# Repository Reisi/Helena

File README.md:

# Helena

Helena is an alternative driver for the Yinding or KD2 Headlight Cycling Lamp.

## Main Features

- Two independant 3A Step-Down current converters.
- Bluetooth connectivity for remote control, configuration and lamp-to-lamp connection.
- Linear power reduction at low battery and high temperature.
- Standby current less than 150µA.
- Supports 1 (one LED), 2 (one or two LEDs) or 3 (up to three LEDs in series) cell Li-Ion battery.
- An integrated motion sensor to control the output current to reduce glare when looking down.
- A multi-functional com pin, can be used for wired communication or an external button.

## License

This project is licensed under the BSD-2-clause License - see the [license.txt](license.txt) file for details

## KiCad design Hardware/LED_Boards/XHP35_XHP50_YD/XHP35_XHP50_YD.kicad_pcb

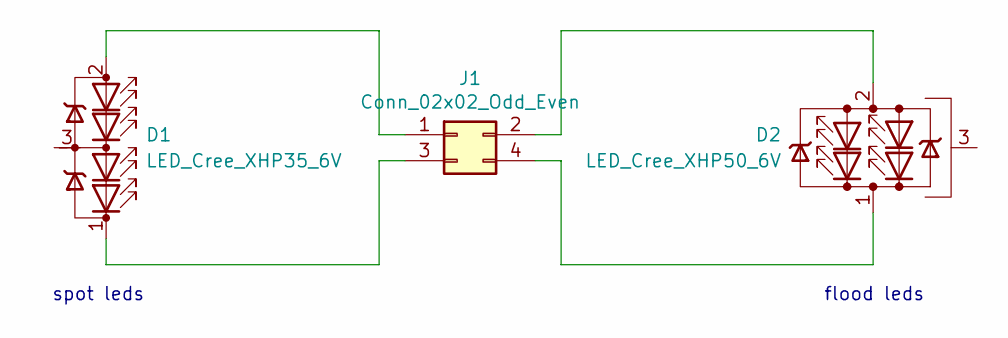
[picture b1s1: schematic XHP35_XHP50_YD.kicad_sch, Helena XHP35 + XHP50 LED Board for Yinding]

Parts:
D1: LED_Cree_XHP35_6V; LED_Cree-XHP50_12V
D2: LED_Cree_XHP50_6V; LED_Cree-XHP50_6V
J1: Conn_02x02_Odd_Even; PinHeader_2x02_P2.00mm_Vertical_SMD

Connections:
unnamed: D1.2 (A), J1.1
unnamed: D1.1 (K), J1.3
unnamed: D2.2 (A), J1.2
unnamed: D2.1 (K), J1.4

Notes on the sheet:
flood leds
spot leds

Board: 2 copper layers, 3 parts (0 on the bottom side), 4 nets, no tracks yet.

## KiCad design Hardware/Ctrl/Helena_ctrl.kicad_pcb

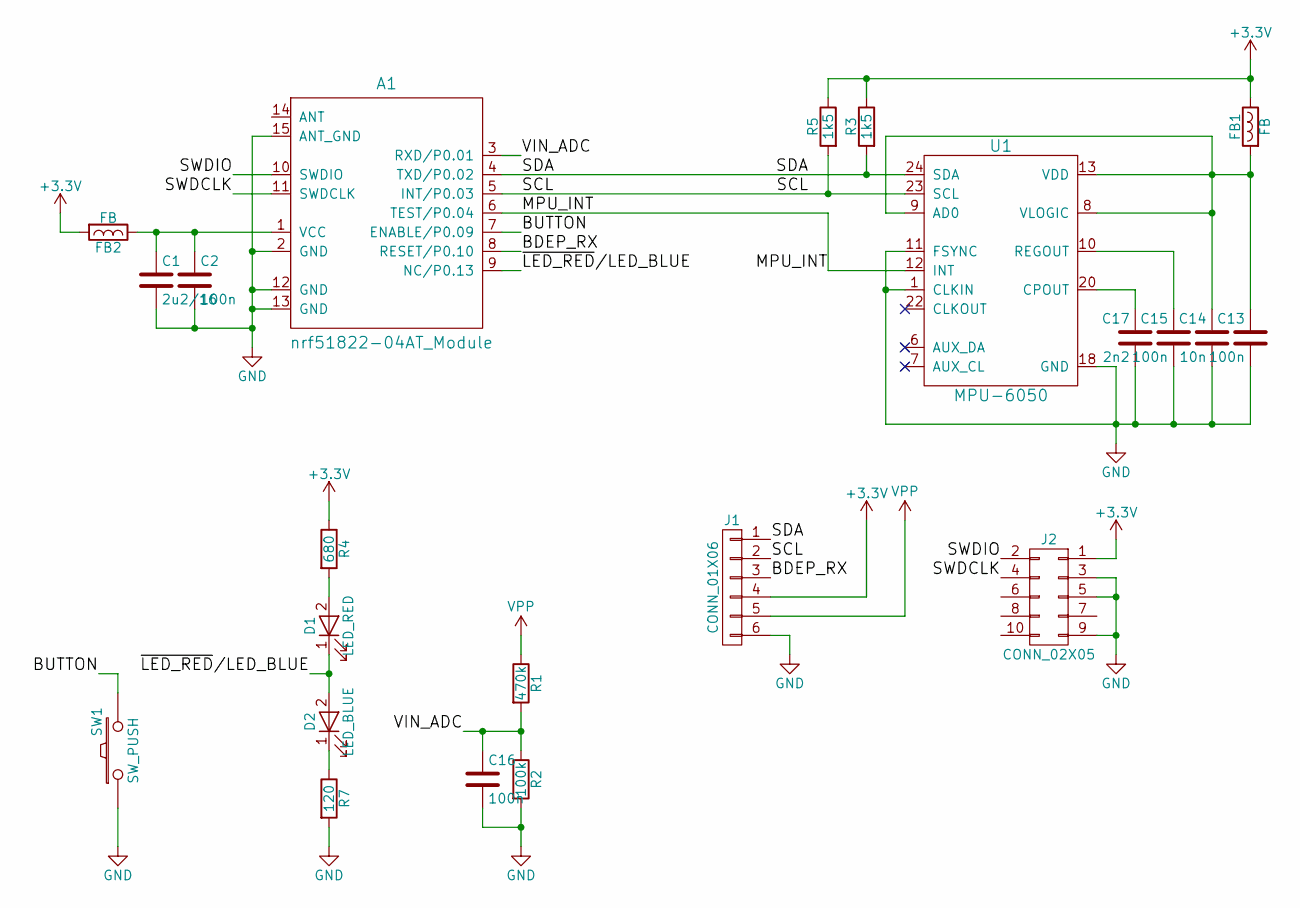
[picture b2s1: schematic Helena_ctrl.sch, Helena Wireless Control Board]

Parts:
A1: nrf51822-04AT_Module; WT51822-S4AT
C1: 2u2/16; C_0603_1608Metric
C2, C13, C15, C16: 100n; C_0603_1608Metric
C14: 10n; C_0603_1608Metric
C17: 2n2; C_0603_1608Metric
D1: LED_RED; D_0603_1608Metric
D2: LED_BLUE; D_0603_1608Metric
FB1, FB2: FB; L_0603_1608Metric
J1: CONN_01X06; PinHeader_1x06_P2.00mm_Vertical
J2: CONN_02X05; PinHeader_2x05_P1.27mm_Vertical
R1: 470k; R_0603_1608Metric
R2: 100k; R_0603_1608Metric
R3, R5: 1k5; R_0603_1608Metric
R4: 680; R_0603_1608Metric
R7: 120; R_0603_1608Metric
SW1: SW_PUSH; JTP-1138EM
U1: MPU-6050; QFN-24_4x4mm_Pitch0.5mm

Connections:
+3V3: FB1.1, FB2.2, J1.4, J2.1, R3.1, R4.1, R5.1
/BDEP_RX: A1.8 (RESET/P0.10), J1.3
/BUTTON: A1.7 (ENABLE/P0.09), SW1.2
/MPU_INT: A1.6 (TEST/P0.04), U1.12 (INT)
/SCL: A1.5 (INT/P0.03), J1.2, R5.2, U1.23 (SCL)
/SDA: A1.4 (TXD/P0.02), J1.1, R3.2, U1.24 (SDA)
/SWDCLK: A1.11 (SWDCLK), J2.4
/SWDIO: A1.10 (SWDIO), J2.2
/VIN_ADC: A1.3 (RXD/P0.01), C16.1, R1.2, R2.1
/~LED_RED~/LED_BLUE: A1.9 (NC/P0.13), D1.1 (K), D2.2 (A)
GND: A1.2 (GND), A1.12 (GND), A1.13 (GND), A1.15 (ANT_GND), C1.2, C2.2, C13.2, C14.2, C15.2, C16.2, C17.2, J1.6, J2.3, J2.5, J2.9, R2.2, R7.2, SW1.1, U1.1 (CLKIN), U1.11 (FSYNC), U1.18 (GND)
unnamed: A1.1 (VCC), C1.1, C2.1, FB2.1
unnamed: C13.1, C14.1, FB1.2, U1.8 (VLOGIC), U1.9 (AD0), U1.13 (VDD)
unnamed: C15.1, U1.10 (REGOUT)
unnamed: C17.1, U1.20 (CPOUT)
unnamed: D1.2 (A), R4.2
unnamed: D2.1 (K), R7.1
VPP: J1.5, R1.1

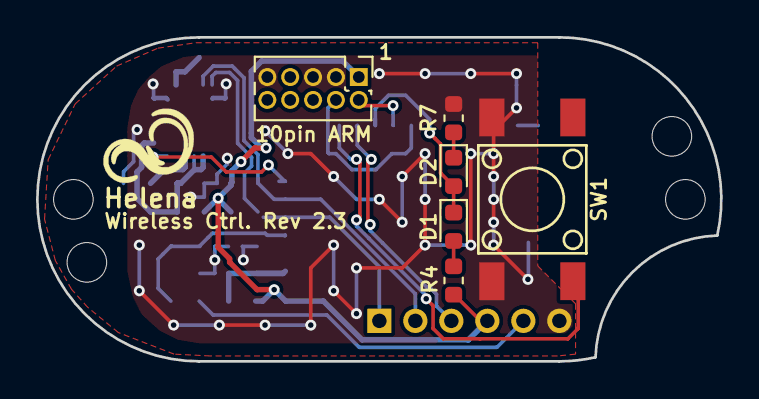
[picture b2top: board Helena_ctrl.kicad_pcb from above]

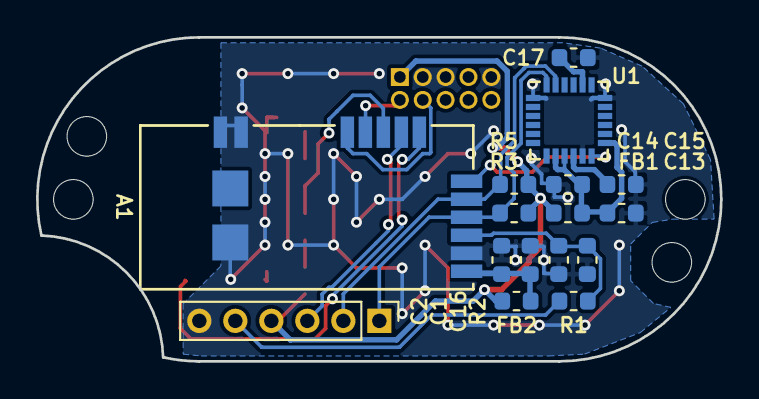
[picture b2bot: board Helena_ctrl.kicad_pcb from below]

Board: 2 copper layers, 38.0 x 18.0 mm, 22 parts (16 on the bottom side), 18 nets.

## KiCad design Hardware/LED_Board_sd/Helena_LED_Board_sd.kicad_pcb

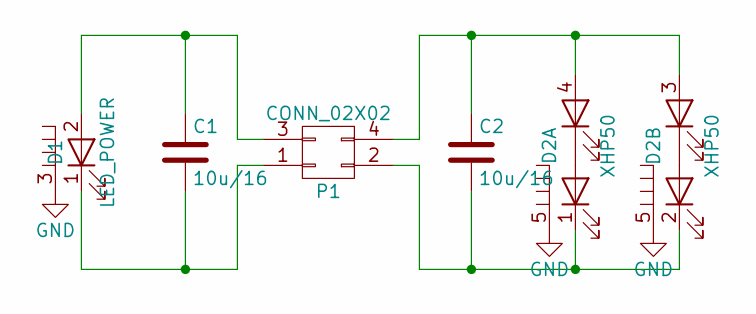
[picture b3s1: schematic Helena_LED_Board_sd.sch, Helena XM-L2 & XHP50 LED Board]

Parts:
C1, C2: 10u/16; C_0805
D1: LED_POWER; LED_CREE-XML
D2: XHP50; LED_CREE-XHP50
P1: CONN_02X02; Pin_Header_Straight_2x02_2.00_Pitch

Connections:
GND: D1.3 (HS), D2.5 (HS)
unnamed: C1.1, D1.2 (A), P1.3
unnamed: C1.2, D1.1 (K), P1.1
unnamed: C2.1, D2.3 (A), D2.4 (A), P1.4
unnamed: C2.2, D2.1 (K), D2.2 (K), P1.2

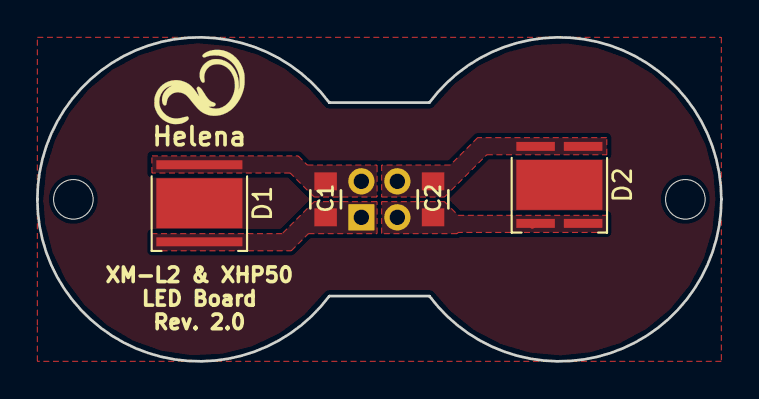
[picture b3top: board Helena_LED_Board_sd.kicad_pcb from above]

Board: 2 copper layers, 38.0 x 18.0 mm, 5 parts (1 on the bottom side), 5 nets.

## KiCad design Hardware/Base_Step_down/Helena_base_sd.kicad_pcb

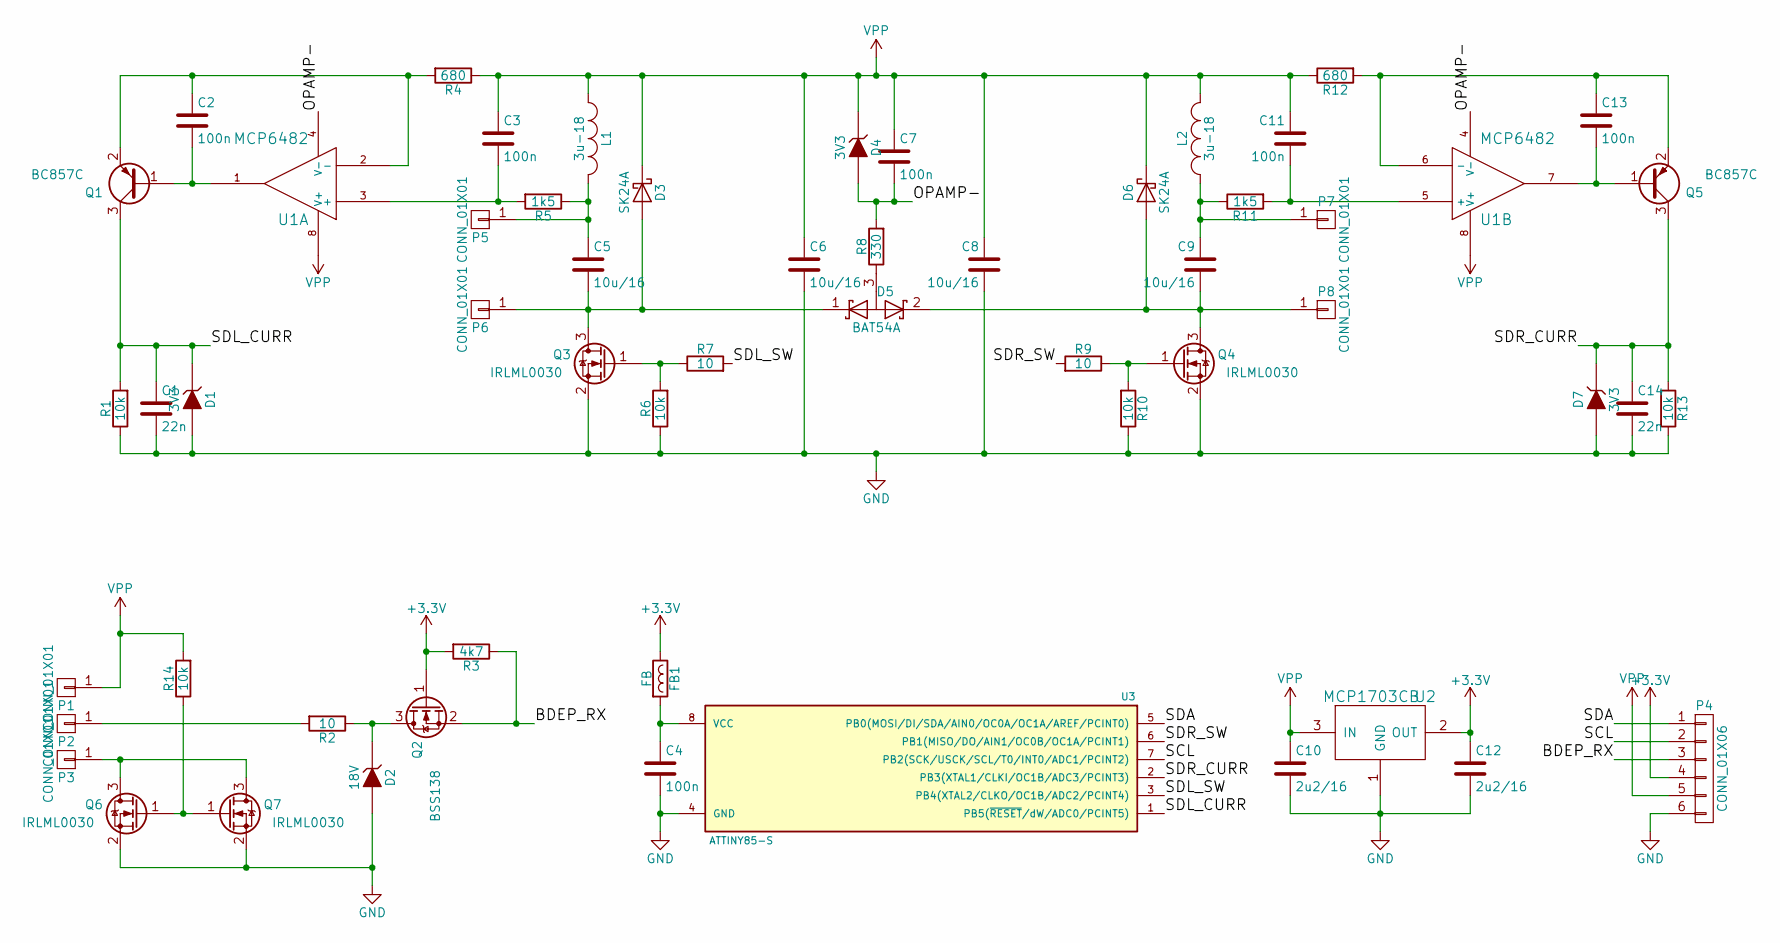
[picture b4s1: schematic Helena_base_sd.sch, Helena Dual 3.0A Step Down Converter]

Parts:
C1, C14: 22n; C_0603_1608Metric
C2, C3, C4, C7, C11, C13: 100n; C_0603_1608Metric
C5, C9: 10u/16; C_0805_2012Metric
C6, C8: 10u/16; C_1206_3216Metric
C10, C12: 2u2/16; C_0603_1608Metric
D1, D4, D7: 3V3; SOT-23
D2: 18V; SOT-23
D3, D6: SK24A; D_SMA
D5: BAT54A; SOT-23
FB1: FB; L_0603_1608Metric
L1, L2: 3u-18; Choke_SMD_Fastron_242418_FPS
P1, P2, P3: CONN_01X01; 1,5x3mm_SMD
P4: CONN_01X06; Pin_Header_Straight_1x06_2.00_Pitch
P5, P6, P7, P8: CONN_01X01; MILLMAX_5660
Q1, Q5: BC857C; SOT-23
Q2: BSS138; SOT-23
Q3, Q4, Q6, Q7: IRLML0030; SOT-23
R1, R6, R10, R13, R14: 10k; R_0603_1608Metric
R2, R7, R9: 10; R_0603_1608Metric
R3: 4k7; R_0603_1608Metric
R4, R12: 680; R_0603_1608Metric
R5, R11: 1k5; R_0603_1608Metric
R8: 330; R_0603_1608Metric
U1: MCP6482; MSOP-8_3x3mm_P0.65mm
U2: MCP1703CB; SOT-23W
U3: ATTINY85-S; SOIC-8_5.23x5.23mm_P1.27mm

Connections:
+3V3: C12.1, FB1.1, P4.4, Q2.1 (G), R3.2, U2.2 (OUT)
/BDEP_RX: P4.3, Q2.2 (S), R3.1
/OPAMP-: C7.2, D4.1 (A), R8.2, U1.4 (V-)
/SCL: P4.2, U3.7 (PB2(SCK/USCK/SCL/T0/INT0/ADC1/PCINT2))
/SDA: P4.1, U3.5 (PB0(MOSI/DI/SDA/AIN0/OC0A/OC1A/AREF/PCI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)
/SDL_CURR: C1.1, D1.3 (K), Q1.3 (C), R1.2, U3.1 (PB5(~RESET~/dW/ADC0/PCINT5))
/SDL_SW: R7.2, U3.3 (PB4(XTAL2/CLKO/OC1B/ADC2/PCINT4))
/SDR_CURR: C14.1, D7.3 (K), Q5.3 (C), R13.2, U3.2 (PB3(XTAL1/CLKI/OC1B/ADC3/PCINT3))
/SDR_SW: R9.2, U3.6 (PB1(MISO/DO/AIN1/OC0B/OC1A/PCINT1))
GND: C1.2, C4.2, C6.2, C8.2, C10.2, C12.2, C14.2, D1.1 (A), D2.1 (A), D7.1 (A), P4.6, Q3.2 (S), Q4.2 (S), Q6.2 (S), Q7.2 (S), R1.1, R6.1, R10.1, R13.1, U2.1 (GND), U3.4 (GND)
unnamed: C2.1, Q1.2 (E), R4.2, U1.2 (-)
unnamed: C2.2, Q1.1 (B), U1.1
unnamed: C3.2, R5.2, U1.3 (+)
unnamed: C4.1, FB1.2, U3.8 (VCC)
unnamed: C5.1, L1.2, P5.1, R5.1
unnamed: C5.2, D3.2 (A), D5.1 (K), P6.1, Q3.3 (D)
unnamed: C9.1, L2.2, P7.1, R11.1
unnamed: C9.2, D5.2 (K), D6.2 (A), P8.1, Q4.3 (D)
unnamed: C11.2, R11.2, U1.5 (+)
unnamed: C13.1, Q5.2 (E), R12.2, U1.6 (-)
unnamed: C13.2, Q5.1 (B), U1.7
unnamed: D2.3 (K), Q2.3 (D), R2.1
unnamed: D5.3 (A), R8.1
unnamed: P2.1, R2.2
unnamed: P3.1, Q6.3 (D), Q7.3 (D)
unnamed: Q3.1 (G), R6.2, R7.1
unnamed: Q4.1 (G), R9.1, R10.2
unnamed: Q6.1 (G), Q7.1 (G), R14.1
VPP: C3.1, C6.1, C7.1, C8.1, C10.1, C11.1, D3.1 (K), D4.3 (K), D6.1 (K), L1.1, L2.1, P1.1, P4.5, R4.1, R12.1, R14.2, U1.8 (V+), U2.3 (IN)

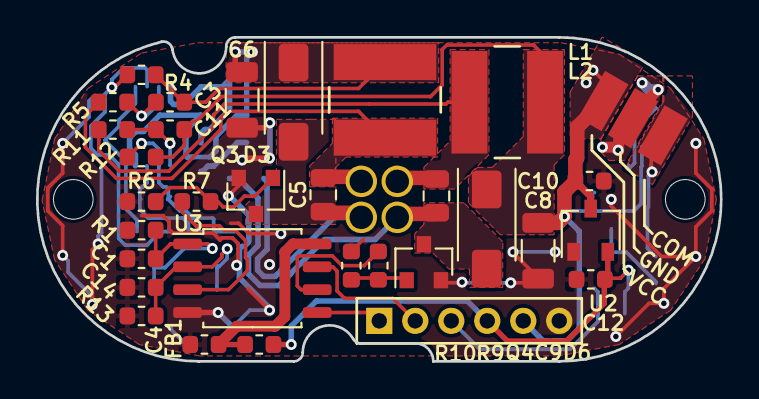
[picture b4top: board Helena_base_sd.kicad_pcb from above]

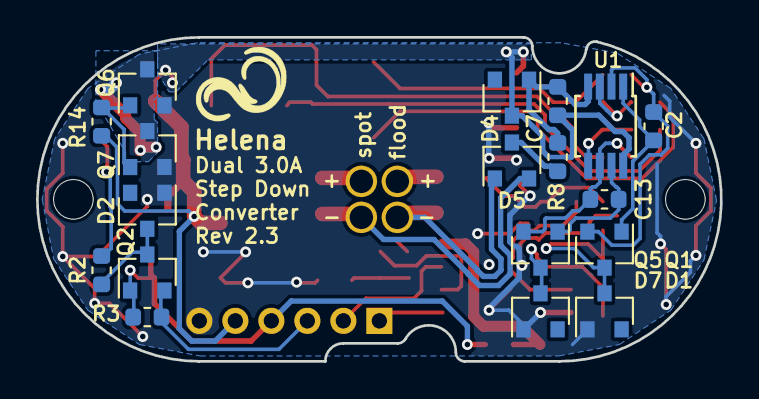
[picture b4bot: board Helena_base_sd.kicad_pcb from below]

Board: 2 copper layers, 38.0 x 18.0 mm, 56 parts (18 on the bottom side), 29 nets.

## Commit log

2017-01-15 reworked limiter (reduced flickering), improved power management and cable communication
2017-01-20 added cloned modes to use both drivers for spot or flood
2017-01-21 added configuration helper file
2017-01-23 fixed com lockup bug and flickering with cold battery
2017-01-30 added led configuration detection and user manual
2017-01-30 minor changes in readme
2017-01-31 added sensor offset calibration
2017-02-22 added brake detection (still experimental)
2017-02-27 added reverse polarity protection and led board
2018-11-16 added independent configurable current limit
2019-02-26 updated control board
2019-10-29 Hardware update for better compatibility with KD2 style lights
2019-11-04 light module rework including new limiter, prepared 1 and 3 cell support
2019-11-07 Setup changed (and extended) from enumeration to flags
2019-11-14 implemented daisy chain feature
2019-11-15 added taillight and brake indicator
2019-11-16 added low power motion interrupt to wakeup lamp when moving
2019-11-17 preferred mode configuration added
2019-11-22 debug report on notification enable, hmi interface handles remote buttons, prepared btle to read inclination of connected light
2019-11-25 added driver calibration over i2c
2019-12-03 fixed failed garbage collection bug, driver firmware update, doku update
2019-12-10 improved debug interface
2020-03-11 reworked debug interface
2021-03-25 added billy support
2021-03-28 separate storage key for billy mode configuration
2021-04-04 minor bugfixes
2021-04-18 added support for R51 remote
2021-04-21 status led blinking
2021-04-22 added battery soc and taillight power to measurement notification
2021-04-23 added temporary mode
2021-04-23 factory reset with button
2021-05-02 added SOS mode
2021-05-30 several bugfixes
2022-07-24 add support for Pearl/Auviso Remote, bugfixes, build instructions, ...
2024-06-17 v3 alpha
2025-06-22 fixed hard fault when relaying mode from com interface
